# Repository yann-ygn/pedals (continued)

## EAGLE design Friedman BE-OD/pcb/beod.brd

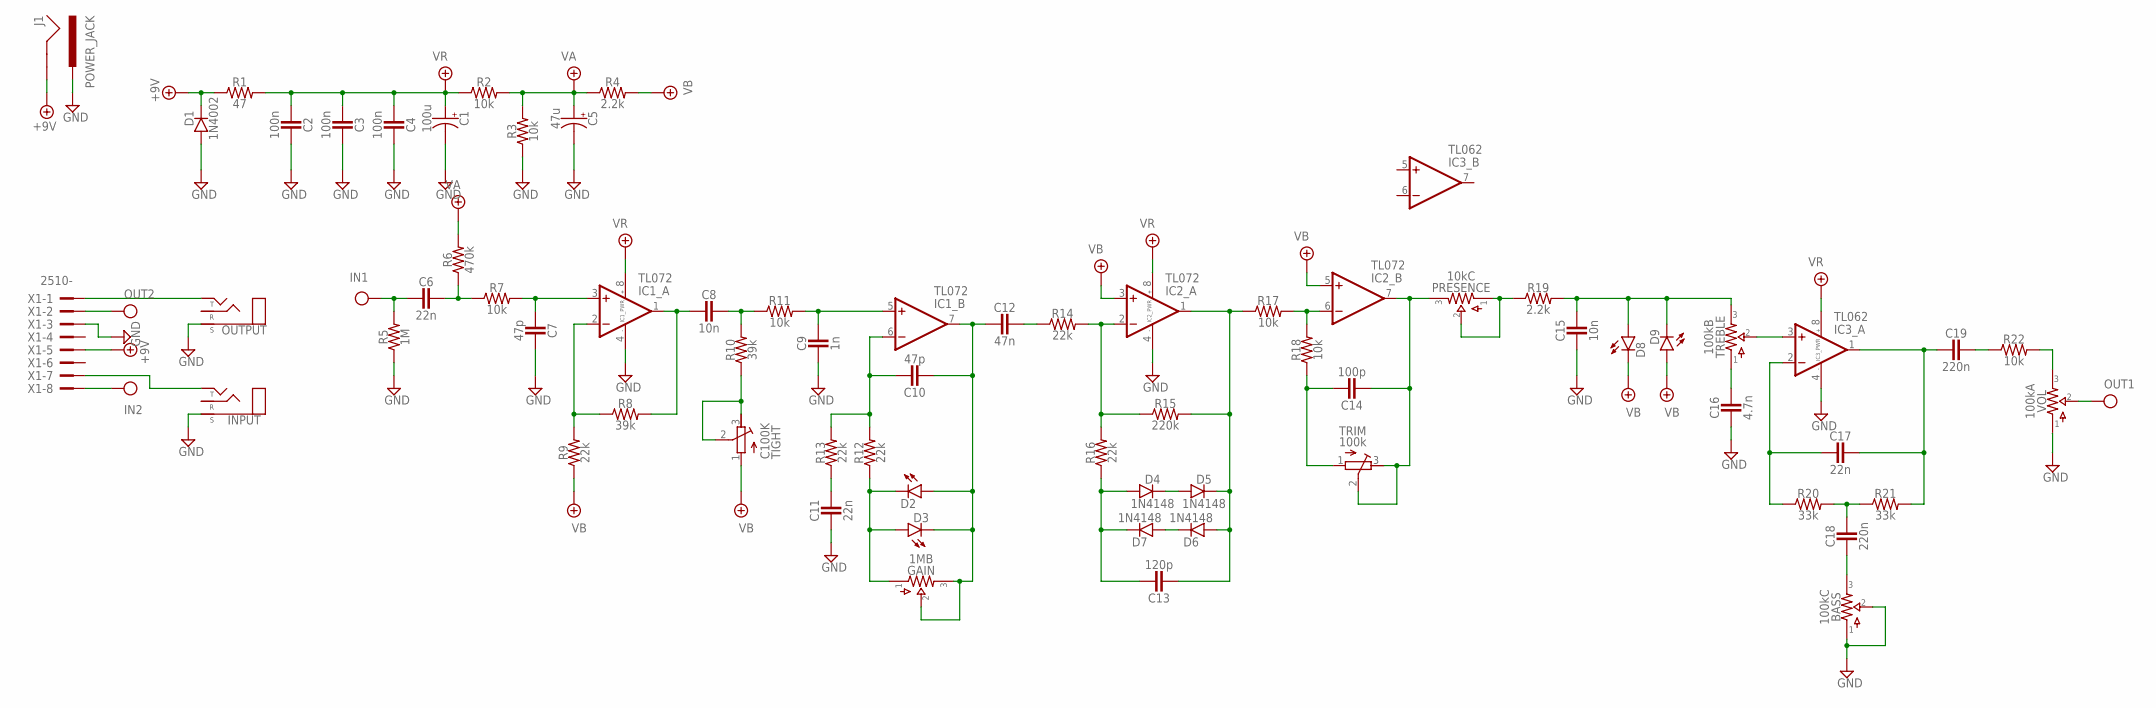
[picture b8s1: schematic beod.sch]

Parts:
BASS: 100kC; 16MM
C1: 100u; 040_020
C2, C3, C4: 100n; 050X030_025_2
C5: 47u; 040_020
C6, C11, C17: 22n; BOX_SMALL
C7, C10: 47p; 050X030_025_2
C8, C15: 10n; BOX_SMALL
C9: 1n; BOX_SMALL
C12: 47n; BOX_SMALL
C13: 120p; 050X030_025_2
C14: 100p; 050X030_025_2
C16: 4.7n; BOX_SMALL
C18, C19: 220n; BOX_SMALL
D1: 1N4002; DO41-2
D2, D3, D8, D9: 3mm_RED; 3MM_D
D4, D5, D6, D7: 1N4148; DO35-2
GAIN: 1MB; 16MM
IC1, IC2: TL072; DIL0
IC3: TL062; DIL0
INPUT: STEREONMJ; NMJ6HCD2
J1: POWER_JACK; POWER_JACK_PTH
OUTPUT: STEREONMJ; NMJ6HCD2
PRESENCE: 10kC; 16MM
R1: 47; R0207/3
R2, R3, R7, R11, R17, R18, R22: 10k; R0207/3
R4, R19: 2.2k; R0207/3
R5: 1M; R0207/3
R6: 470k; R0207/3
R8, R10: 39k; R0207/3
R9, R12, R13, R14, R16: 22k; R0207/3
R15: 220k; R0207/3
R20, R21: 33k; R0207/3
TIGHT: C100K; RTRIM3296W
TREBLE: 100kB; 16MM
TRIM: 100k; RTRIM3296W
VOL: 100kA; 16MM
X1: 2510-; PAK100/2500-10

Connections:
+18V: D1.C, J1.GND, R1.1, X1.5
GND: BASS.1, BASS.2, C1.-, C2.1, C3.1, C4.1, C5.-, C7.1, C9.2, C11.2, C15.2, C16.2, D1.A, IC1.4 (V-), IC2.4 (V-), IC3.4 (V-), INPUT.S, J1.PWR, OUTPUT.S, R3.1, R5.1, VOL.1, X1.3
IN: C6.2, R5.2, X1.8
unnamed: INPUT.T, X1.7
unnamed: C6.1, R6.1, R7.1
unnamed: C7.2, IC1.3 (+IN), R7.2
unnamed: OUTPUT.T, X1.1
unnamed: C8.2, IC1.1 (OUT), R8.2
unnamed: IC1.2 (-IN), R8.1, R9.2
unnamed: R10.1, TIGHT.2 (S), TIGHT.3 (E)
unnamed: C8.1, R10.2, R11.1
unnamed: C9.1, IC1.5 (+IN), R11.2
unnamed: C10.1, IC1.6 (-IN), R12.2, R13.2
unnamed: C10.2, C12.2, D2.ANODE (A), D3.P$1 (C), GAIN.2, GAIN.3, IC1.7 (OUT)
unnamed: C14.1, R18.1, TRIM.1 (A)
unnamed: C11.1, R13.1
unnamed: D2.P$1 (C), D3.ANODE (A), GAIN.1, R12.1
unnamed: C14.2, IC2.7 (OUT), PRESENCE.3, TRIM.2 (S), TRIM.3 (E)
unnamed: C12.1, R14.1
unnamed: IC2.2 (-IN), R14.2, R15.1, R16.2
unnamed: C13.1, D4.A, D7.C, R16.1
unnamed: C13.2, D5.C, D6.A, IC2.1 (OUT), R15.2, R17.1
unnamed: D4.C, D5.A
unnamed: D6.C, D7.A
unnamed: IC2.6 (-IN), R17.2, R18.2
unnamed: C15.1, D8.ANODE (A), D9.P$1 (C), R19.2, TREBLE.3
unnamed: PRESENCE.1, PRESENCE.2, R19.1
unnamed: C16.1, TREBLE.1
unnamed: C17.2, IC3.2 (-IN), R20.1
unnamed: C17.1, C19.2, IC3.1 (OUT), R21.2
unnamed: C18.1, R20.2, R21.1
unnamed: BASS.3, C18.2
unnamed: IC3.3 (+IN), TREBLE.2
unnamed: C19.1, R22.1
unnamed: R22.2, VOL.3
OUT: VOL.2, X1.2
VA: C5.+, R2.2, R3.2, R4.1, R6.2
VB: D8.P$1 (C), D9.ANODE (A), IC2.3 (+IN), IC2.5 (+IN), R4.2, R9.1, TIGHT.1 (A)
VR: C1.+, C2.2, C3.2, C4.2, IC1.8 (V+), IC2.8 (V+), IC3.8 (V+), R1.2, R2.1

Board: 2 copper layers, 65 parts (1 on the bottom side), 39 nets, no tracks yet.

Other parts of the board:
U$2: 125B_PCB_HUGE

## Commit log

2017-04-25 20170425
2017-05-05 20170505
2017-07-12 20170712
2017-07-26 20170726
2017-08-12 20170812
2017-08-13 20170813
2017-08-21 20170821
2017-08-24 20170824
2017-09-02 20170902
2017-09-14 20170914
2017-10-03 20171003
2017-10-09 20171009
2017-10-19 20171019
2017-10-20 20171020
2017-10-23 20171023
2017-10-23 20171023-01
2017-10-25 20171025
2017-11-02 20171102
2017-11-06 20171106
2017-11-07 20171107
2017-11-08 20171108
2017-11-11 20171111
2017-11-20 20171120
2017-12-16 20171216
2017-12-20 20171220
2017-12-25 20171225
2017-12-30 20171230
2018-01-02 20180102
2018-01-19 20170119
2018-01-25 20180125
2018-02-07 20180207
2018-05-29 20180529
2018-08-03 20180803
2018-09-10 20180910
2018-12-01 20181201
2018-12-10 20181210/10:32
2019-01-16 20190116/11:48
2019-01-18 20190118/11:21
2019-08-02 20190802/11:14
2019-09-02 20190902/11:06
2020-03-17 20200317/09:25
2020-03-19 20200319/09:11
2020-03-19 20200319/10:14
2020-03-20 20200320/09:17
2020-03-22 20200322/09:12
2020-03-23 20200323/10:20
2020-03-24 20200324/10:36
2020-03-25 20200325/10:41
2020-03-26 20200326/09:53
2020-03-27 20200327/10:23
2020-03-29 20200329/10:01
2020-03-29 20200329/10:32
2021-05-17 20210517/09:48
2021-05-18 20210518/09:48
2021-11-11 20211111/21:24
2021-11-12 20211112/22:07
2021-11-13 20211113/19:27
2022-02-24 20220224/22:07
